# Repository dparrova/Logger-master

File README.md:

# Datalogger Secador de alimentos
## Contenido
En este repositorio encontrará:

* Lista de componente
* Esquematicos / Archivos
  * Archivo PCB para fabribar
  * Archivo de para subir al arduino
  * Archivos del modelo 3D de la caja
* Funcionamiento
* Sonidos
* Errores
* repositorio https://github.com/dparrova/Logger-master 

## Listado de componentes
para el desarrollo del Datalogger se usaron los siguiente modulos

* placa de Arduino Nano
* modulo de RTC
* modulo de Micro SD
* modulo DTH11
* modulo de sensor de temeratura MAX667
* micro SD
* conecotr de RJ45
* cable de dato upt RJ45

## Esquematicos / Archivos
Dendro de la carpeta de Archivos se encuentran los esquematicos, modelos de la caja en archivos STL para la impreción en 3D, tambien los archivo Gerber para la impresión de la placa.

## Funcionamiento
El dispositivo cuenta con alimentación proporcinada por cuatro baterias AA. Almacena datos cada minuto de dos temperaturas, una humedad relativa y la fecha y hora de cada dato. Emite sonidos de como idicador de errores o procesos satisfactorios, se neciende y apaga con el interrutor lateral.

### Crear archivo Datos.csv 
Teniendo la memoria dentro del dispositivo, se verifica que exista el archivo Datos.csv, si no existe, lo crea automaticamente y comienza a guardar datos.

### Procedimiento de apagado/encendido
Apague o encienda el dispositivo con el interruptor ubicado en la parte lateral.

### Procedimdiento de toma de datos
Primero coloque las baterias en el porta baterias. 
Coloque tambien la memoria microSD en la ranura. Esta memoria debe tener en su interior un archivo llamado Datos.csv.
Conecte el cable de datos al dispositivo mediante el conector de red.
Encienda el dispositivo con el interruptor ubicado en la parte lateral.
El dispositivo realizara sonidos (ver la sección de *sonidos*)
Los datos se tomaran cada minuto

### Recolección de datos
Con el dispositivo apagado, retire la memoria microSD del dispositivo, use un adaptador microSD/USB para transferir los datos al computador, haga una copia del archivo Datos.csv a su equipo.

Asegurese de no abrir directamente el archivo que se encuentra en memoria desde Excel o cualquier otro programa que modifque el tipo de archivo.

## Sonidos
Se integra un buzzer para tener una ayuda auditiva para identificar acciones
* Un pitido (cada minuto) : indica que el dispositivo almacenó los datos correctamente, este tiene un intervalo de un minuto
* Dos pitidos (repetitivos) : indica que no encuentra la memora microSD conectada o que hay un error.

### Errores comunes
* Reconoce el archivo Datos.csv pero no guarda información
  * Solución: elimine el archivo y vuelvalo a crear.
* Alacena datos pero con el errores en la fecha
  * Solución : configurar el reloj,
  * Remplace la bateria y compile de nuevo el archivo al arduino.
* En cada reinicio del dispositivo se desconfigura la fecha y hora
  * Cambiar la bateria del RTC, esto se hace abriendo la caja y cambiado la bateria redonda.

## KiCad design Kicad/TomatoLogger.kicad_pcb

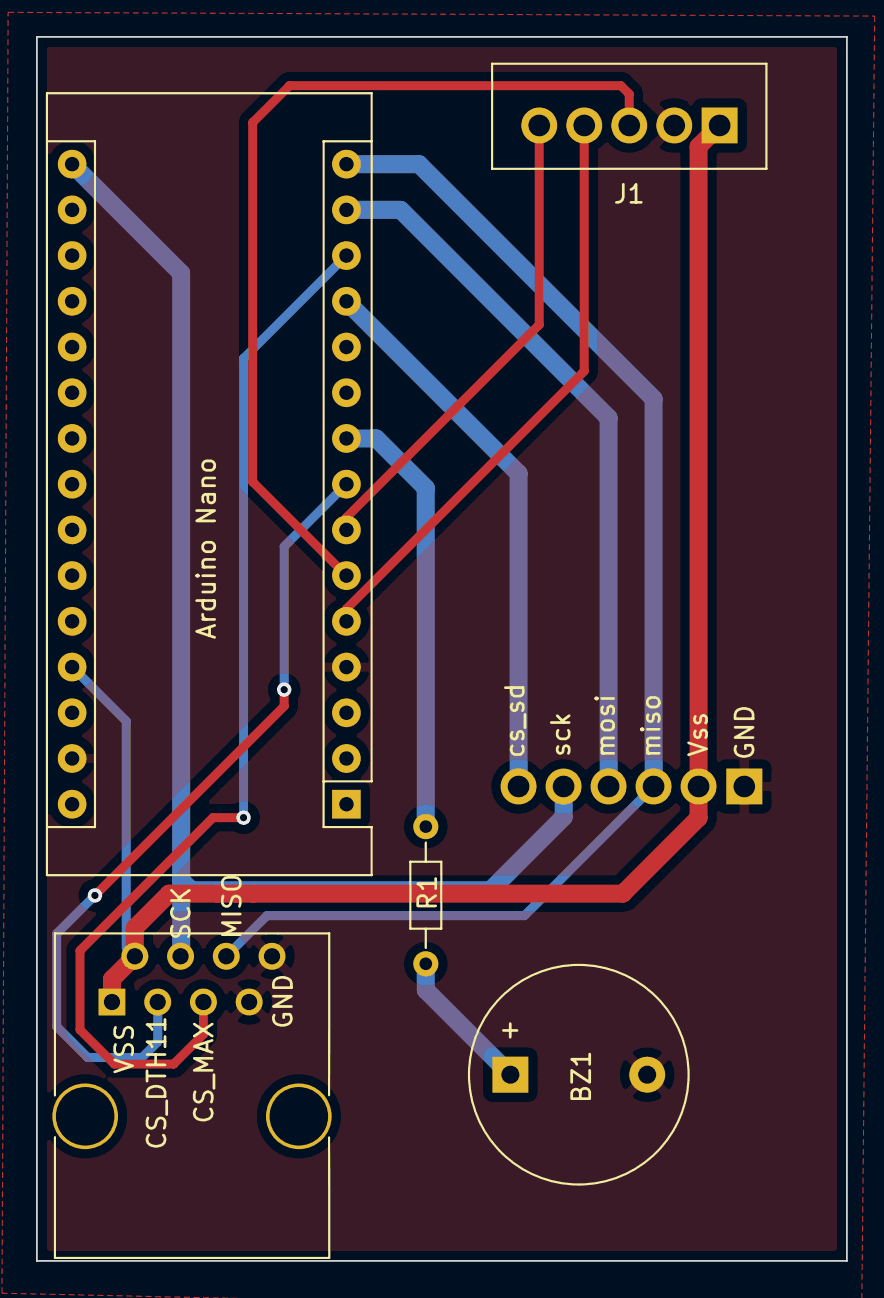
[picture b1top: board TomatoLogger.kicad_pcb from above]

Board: 2 copper layers, 45.0 x 68.0 mm, 6 parts (1 on the bottom side), 13 nets.

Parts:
Arduino Nano: Arduino_Nano_v2.x; Arduino_Nano
BZ1: Buzzer; Buzzer_12x9.5RM7.6
J1: RCT; Wafer_Vertical15x5.8x7RM2.5-5
J2: SD; Wafer_Vertical17.5x5.8x7RM2.5-6
J3: SENSOR; RJ45_8
R1: R; R_Axial_DIN0204_L3.6mm_D1.6mm_P7.62mm_Horizontal

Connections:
5V: Arduino Nano.27, J1.1, J2.2, J3.1, J3.2
Buzzer: Arduino Nano.9, R1.1
CLK: Arduino Nano.6, J1.3
CS_DTH11: Arduino Nano.8, J3.3
CS_MAX: Arduino Nano.13, J3.5
CS_RCT: Arduino Nano.5, J1.4
CS_SD: Arduino Nano.12, J2.6
GND: Arduino Nano.4, Arduino Nano.29, BZ1.2, J1.2, J2.1, J3.7, J3.8
MISO: Arduino Nano.15, J2.3, J3.6
MOSI: Arduino Nano.14, J2.4
unnamed: BZ1.1, R1.2
RST: Arduino Nano.7, J1.5
SCK: Arduino Nano.16, J2.5, J3.4

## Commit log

2024-05-03 frist commint
2024-07-15 Archivos agregados
2024-07-15 Archivos STL agregados
